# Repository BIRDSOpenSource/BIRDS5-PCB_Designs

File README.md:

<div align="center">
  
</div>

# BIRDS5-PCB_Designs
 Documentation for the PCB design files used in the boards in the BIRDS5 satellite

## About the BIRDS5 Program:

The Mission Statement of the Project is:

> Build Uganda and Zimbabwe’s first satellite while improving the standardized bus system for future missions, giving continuity to the satellite development of Japan and previous missions from BIRDS-1,2,3 and 4.

The project is led by Kyushu Institute of Technology in Japan and involves students from Uganda, Zimbabwe, Trinidad and Tobago, and Japan.

Satellite Names: Taka (Japan), ZIMSAT-1 (Zimbabwe) and PearlAfricaSat-1 (Uganda)

Stakeholders: Uganda Science, Technology and Innovation Office of the President, Zimbabwe National Geospatial And Space Agency (ZINGSA), and Kyushu Institute of Technology (Kyutech) for Japan.

Project duration: 2018-2022

CubeSat: 1U (10x10x10) cm3, 2U (10x10x20) cm3

Weight: 1.13kg

Launch Date: 21st November 2022

BIRDS-5 has 5 main missions in total; attitude visualisation, Imaging classification Mission (IMG-CLS) and Store & Forward (SF- WARD), Particle Instrument for Nano-satellite(PINO), APRS-Digipeater mission (APRS-DP) 

## Organisation structure
In this repository you will find four main folders
```bash
├── .gitattributes
├── Antenna Panel
│   ├── BIRDS-5_1U_+X-panel_EM_PUPV_v3.2.brd
│   ├── BIRDS-5_1U_+X-panel_EM_PUPV_v3.2.sch
│   ├── BIRDS-5_2U_+X-panel_EM_PUPV_v3.2.brd
│   └── BIRDS-5_2U_+X-panel_EM_PUPV_v3.2.sch
├── Back Plane Board
│   ├── BPB_FM1.brd
│   └── BPB_FM1.sch
├── LICENSE
├── README.md
├── Rear Access Board
│   ├── 1U_Rear_Access_Board
│   └── 2U_Rear_Access_Board
└── Solar Panel
    ├── EM Solar Panels
    │   ├── 1U PCB Designs
    │   ├── 2U PCB Designs
    │   └── Solar Attachment Training
    │       └── From Victor
    └── FM Solar Panels
        ├── 1U Solar Panels Data-2022_05_19
        │   ├── 1U Solar Panel PCBs
        │   ├── BOM
        │   ├── Drill Data
        │   │   ├── +Y
        │   │   │   └── CAMOutputs
        │   │   │       └── GerberFiles
        │   │   ├── +Z
        │   │   │   └── CAMOutputs
        │   │   │       └── GerberFiles
        │   │   ├── -X
        │   │   │   └── CAMOutputs
        │   │   │       └── GerberFiles
        │   │   └── -Y
        │   │       └── CAMOutputs
        │   │           └── GerberFiles
        │   ├── Gerber Data
        │   │   ├── +Y
        │   │   │   └── CAMOutputs
        │   │   │       └── GerberFiles
        │   │   ├── +Z
        │   │   │   └── CAMOutputs
        │   │   │       └── GerberFiles
        │   │   ├── -X
        │   │   │   └── CAMOutputs
        │   │   │       └── GerberFiles
        │   │   ├── -Y
        │   │   │   └── CAMOutputs
        │   │   │       └── GerberFiles
        │   │   ├── -Z
        │   │   │   └── CAMOutputs
        │   │   │       └── GerberFiles
        │   │   └── READ ME.txt
        │   ├── Mounting Drawing
        │   │   ├── +Y
        │   │   ├── +Z
        │   │   ├── -X
        │   │   ├── -Y
        │   │   └── -Z
        │   └── PBan_Parts_List
        └── 2U Solar Panels Data-2022_05_19
            ├── 2U Solar Panels PCBs
            ├── BOM
            ├── Drill Data
            │   ├── +Y
            │   │   └── CAMOutputs
            │   │       └── GerberFiles
            │   ├── -Y
            │   │   └── CAMOutputs
            │   │       └── GerberFiles
            │   └── -Z
            │       └── CAMOutputs
            │           └── GerberFiles
            ├── Gerber Data
            │   ├── +Y
            │   │   └── CAMOutputs
            │   │       └── GerberFiles
            │   ├── -Y
            │   │   └── CAMOutputs
            │   │       └── GerberFiles
            │   ├── -Z
            │   │   └── CAMOutputs
            │   │       └── GerberFiles
            ├── Mounting Drawing
            │   ├── +Y
            │   ├── -X
            │   ├── -Y
            │   └── -Z
            └── PBan Parts Lists
```
    
`/Solar Panel` folders contains PCB and schematic file for the 1U and 2U solar panel configurations. Within this folder are also pictures from the Solar Panel Attachment Training to aid in understanding how to attaach the solar cells to the panels. 

## How to use
> [!CAUTION]
> The files `.sch` and `.brd` files in this repositiry were created using Eagle software.
 
For those that want to import these files into 
KiCAD7 [here's how you do it](https://community.element14.com/technologies/open-source-hardware/b/blog/posts/working-with-kicad-7-importing-eagle-files) 
 or KiCAD5.1 [here's how you do it](https://www.youtube.com/watch?v=RBc02MwpKxk&t=1s).

> [!NOTE]
> If you are wondering "What are the .s#1 and .b#1 files?"
> They are EAGLE backup files. Each time you save your work, the previous copy becomes one of them, in case you decide you were being a muppet, or just change your mind.

## I like this project, can I help you?
You are welcome 🙂

* Give us a star ⭐
* Watch repository to be notified about updates 👀
* If you will find some errors, report them in Issues 🐞
* Try Birds designs on some real computer and let us know how it worked in Discussions. 💬
* We would greatly appreciate if you would also tell others about this ecosystem, it helps us to improve BIRDS Open Source. Thank you!

[License for this project](docs/LICENSE.md)

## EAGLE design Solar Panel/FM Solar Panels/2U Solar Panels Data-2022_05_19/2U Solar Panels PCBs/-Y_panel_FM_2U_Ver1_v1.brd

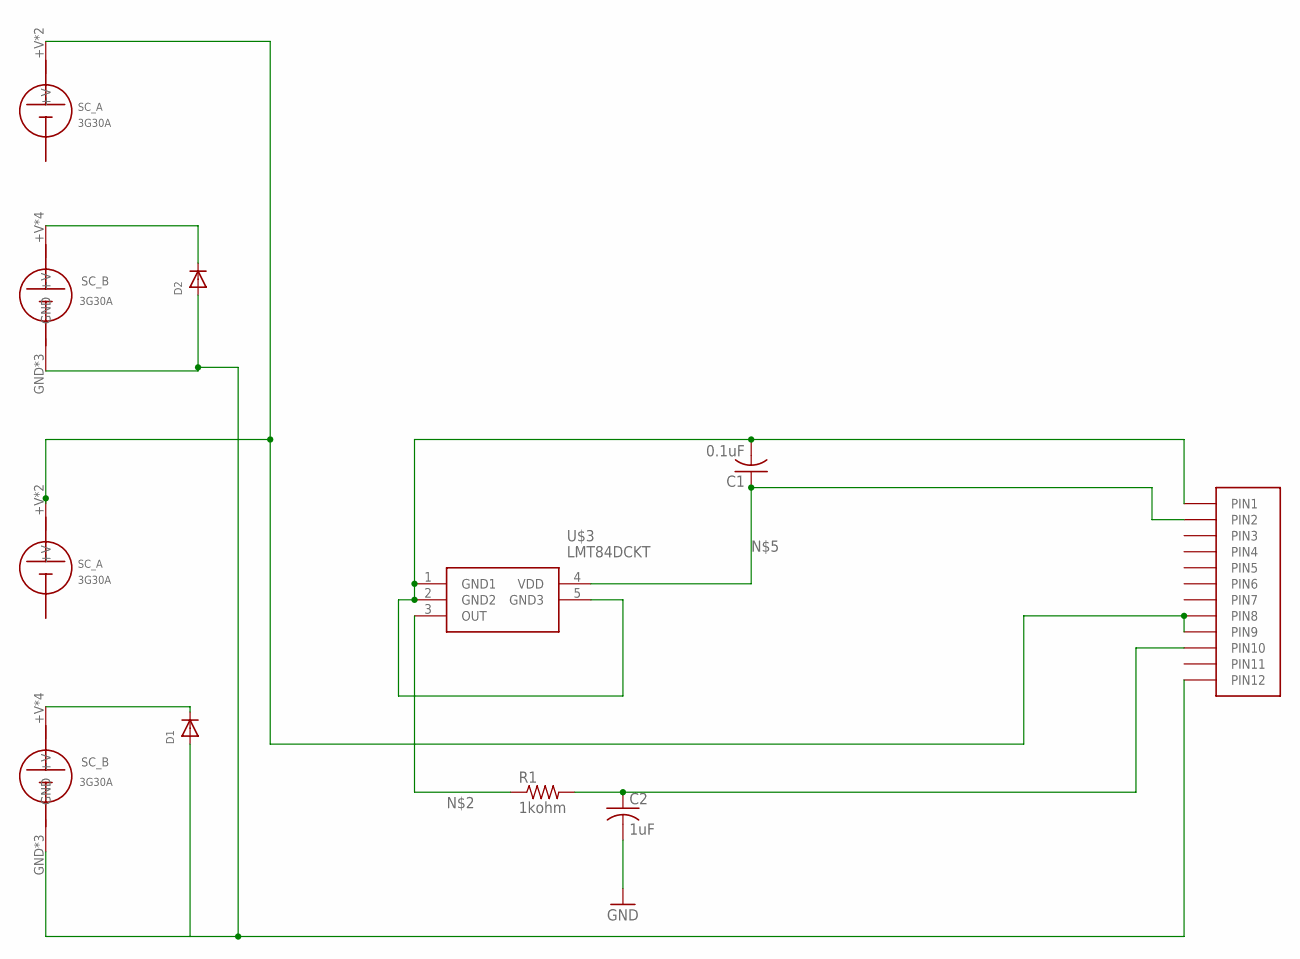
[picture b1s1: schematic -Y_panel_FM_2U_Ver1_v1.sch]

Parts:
C1: 0.1uF; C0805
C2: 1uF; C0805
D1, D2: DIODE_SOD-123FL; SOD-123FL
R1: 1kohm; R0402
SOLARCELL_A, SOLARCELL_A1: SC_A
SOLARCELL_B, SOLARCELL_B1: SC_B
U$1: HEADER12PIN
U$3: LMT84DCKT; SOT65P210X110-5N

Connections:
+V: SOLARCELL_A.+V, SOLARCELL_A.+V1, SOLARCELL_A1.+V, SOLARCELL_A1.+V1, U$1.P8 (PIN8), U$1.P9 (PIN9)
+VB: D1.C, SOLARCELL_B.+V, SOLARCELL_B.+V2 (+V), SOLARCELL_B.+V3 (+V), SOLARCELL_B.+V4 (+V)
GND: C1.2, C2.2, D1.A, D2.A, SOLARCELL_B.GND, SOLARCELL_B.GND1 (GND), SOLARCELL_B.GND2 (GND), SOLARCELL_B1.GND, SOLARCELL_B1.GND1 (GND), SOLARCELL_B1.GND2 (GND), U$1.P1 (PIN1), U$1.P12 (PIN12), U$3.1 (GND1), U$3.2 (GND2), U$3.5 (GND3)
unnamed: D2.C, SOLARCELL_B1.+V, SOLARCELL_B1.+V2 (+V), SOLARCELL_B1.+V3 (+V), SOLARCELL_B1.+V4 (+V)
unnamed: R1.1, U$3.3 (OUT)
unnamed: C1.1, U$1.P2 (PIN2), U$3.4 (VDD)
unnamed: C2.1, R1.2, U$1.P10 (PIN10)

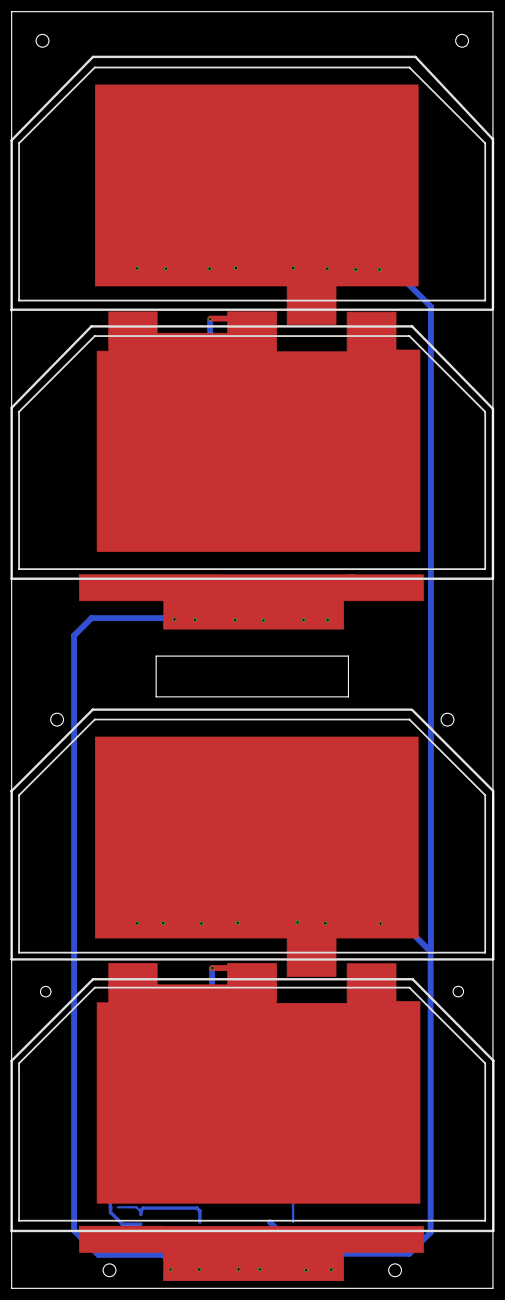
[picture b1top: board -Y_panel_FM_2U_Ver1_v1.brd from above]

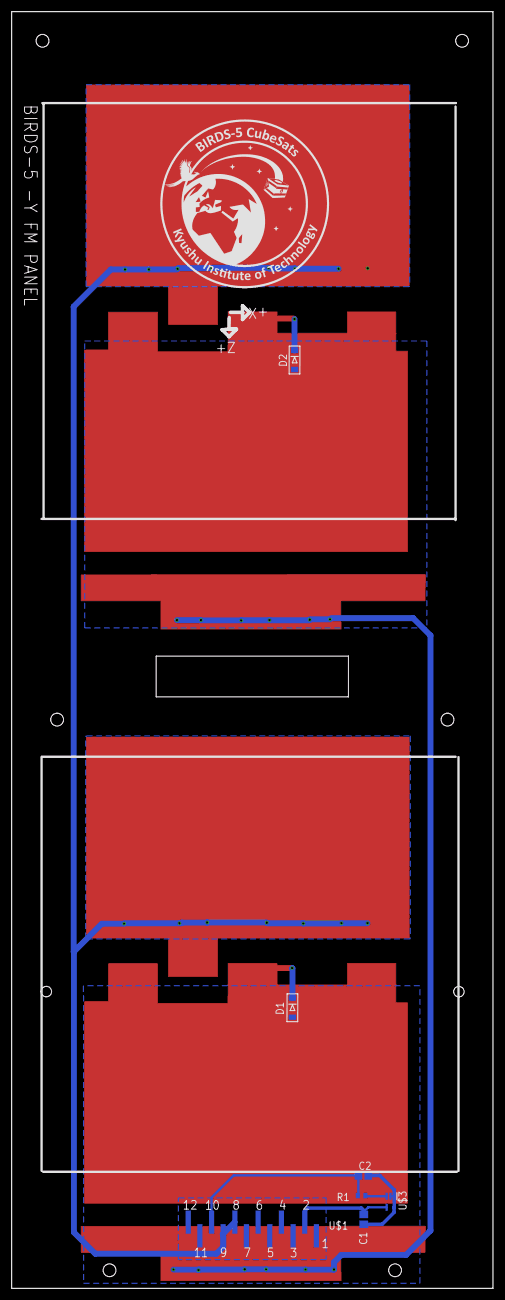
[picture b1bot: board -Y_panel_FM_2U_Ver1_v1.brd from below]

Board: 2 copper layers, 82.6 x 219.1 mm, 11 parts (5 on the bottom side), 7 nets.

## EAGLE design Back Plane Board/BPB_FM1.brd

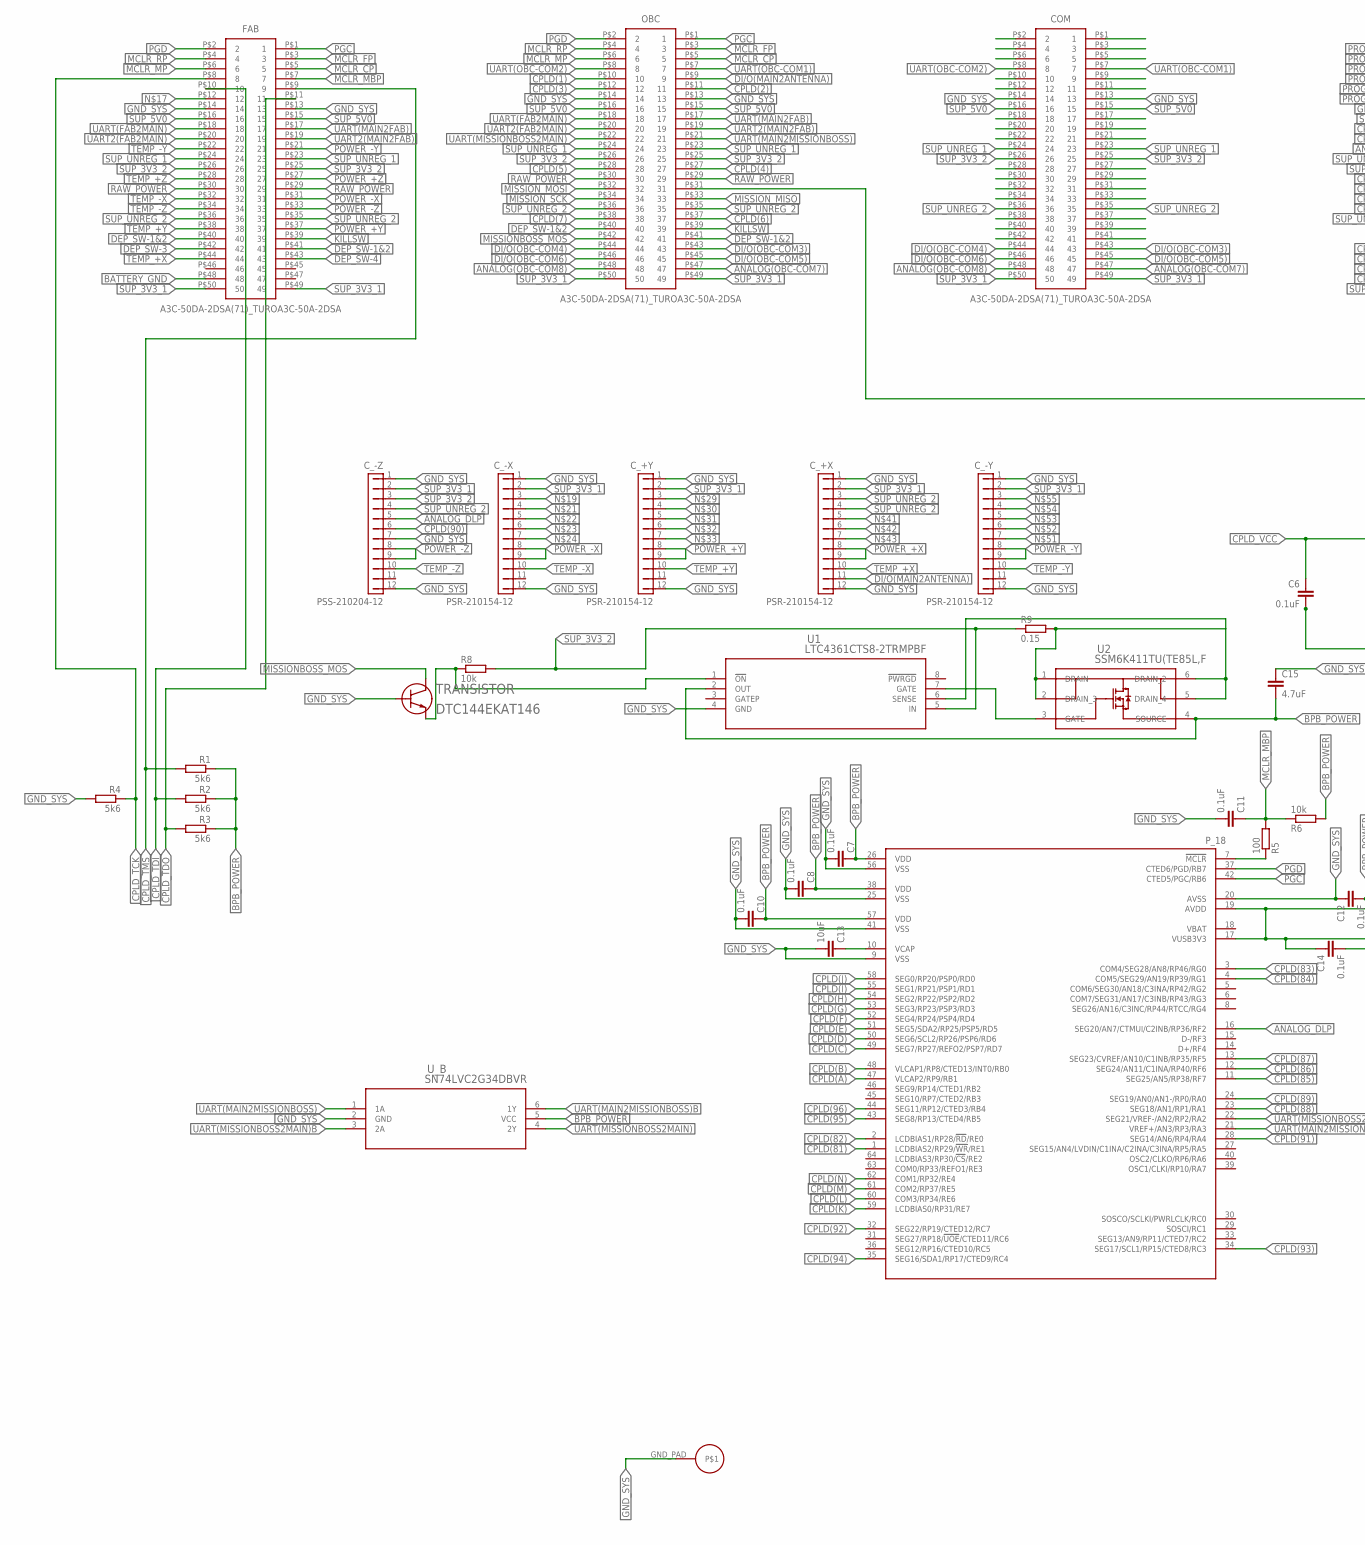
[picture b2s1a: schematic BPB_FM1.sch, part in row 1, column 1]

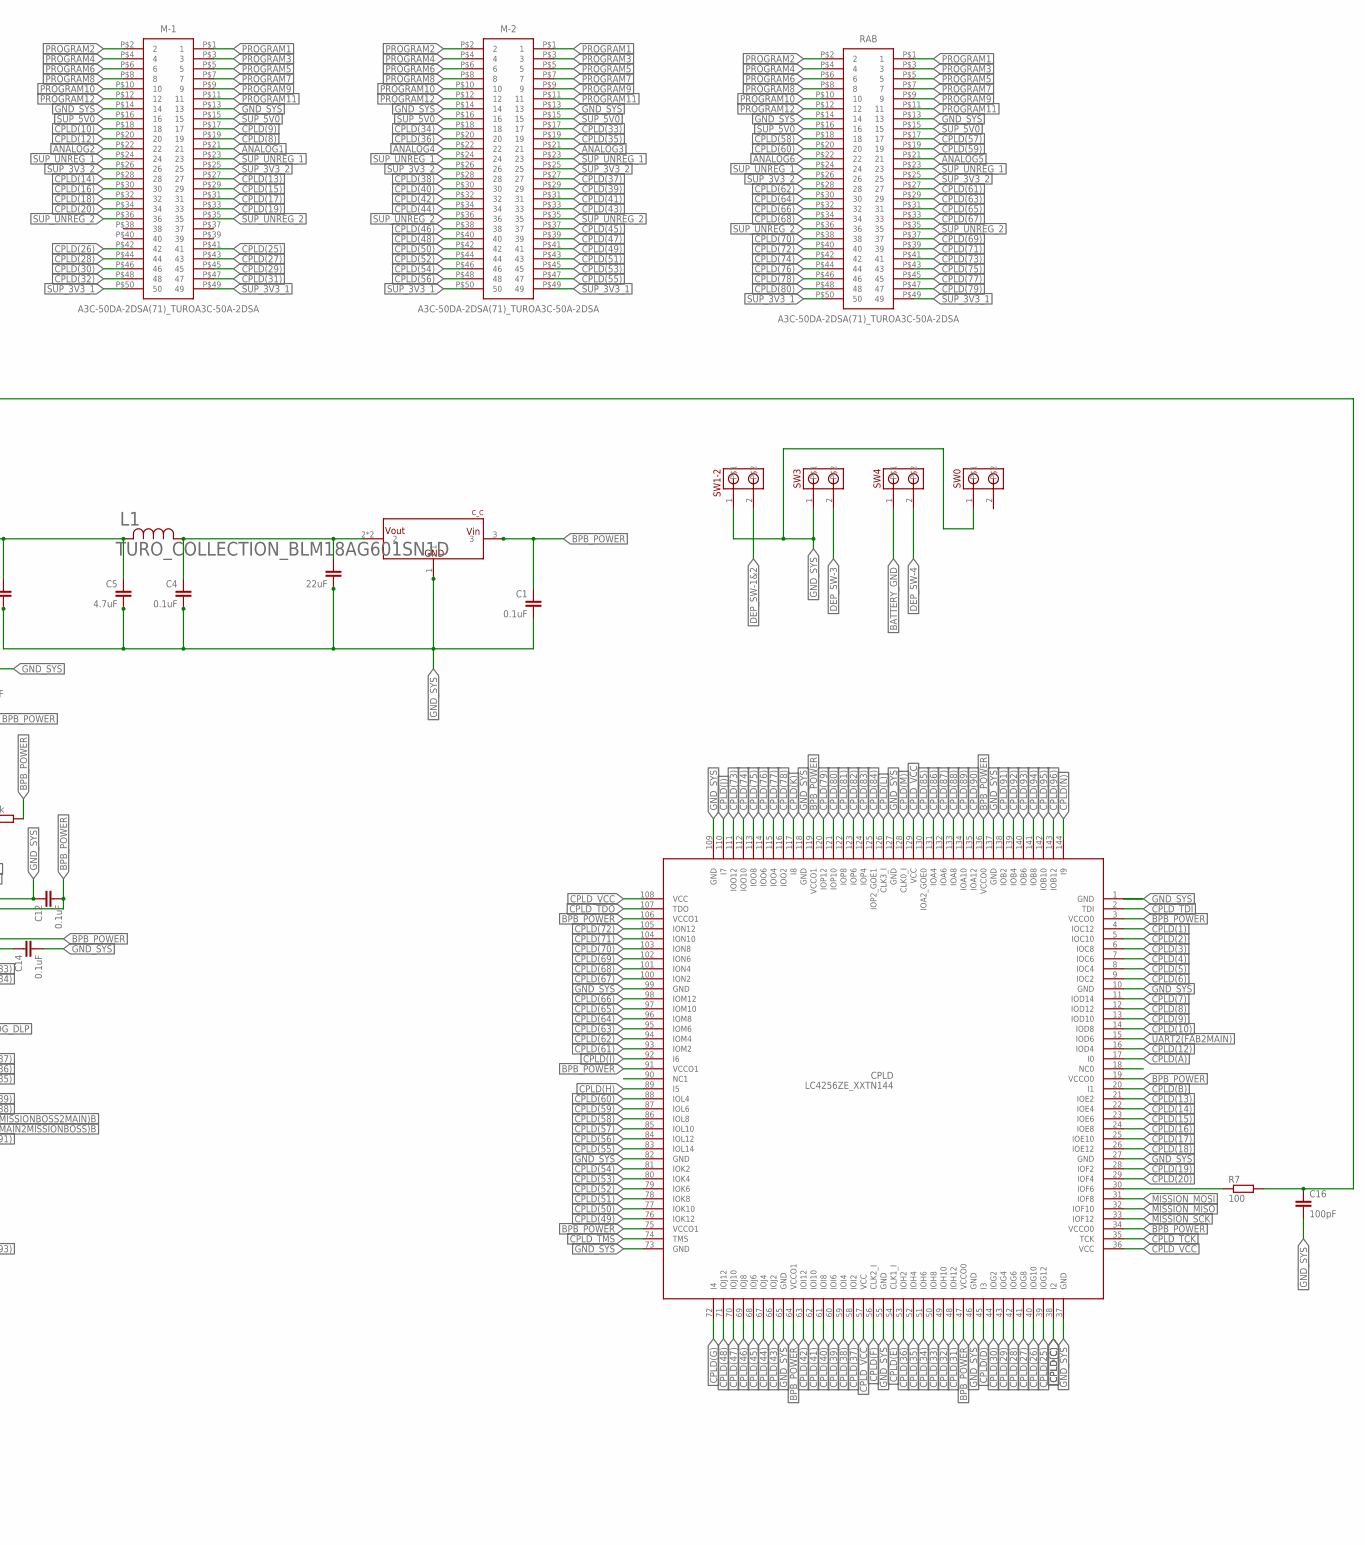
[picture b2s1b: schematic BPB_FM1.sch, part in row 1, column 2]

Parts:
C1, C4, C6, C7, C8, C10, C11, C12, C14: 0.1uF; C0402
C3: 22uF; C2012
C5: 4.7uF; C2012
C13: 10uF; C0402
C15: 4.7uF; C0402
C16: 100pF; C0402
COM: A3C-50DA-2DSA(71)_TUROA3C-50A-2DSA; SHDR50W60P200_2X25_5000X400X44_TR
CPLD: LC4256ZE_XXTN144; TQFP144
C_+X: PSR-210154-12; PIN1X12/90
C_+Y: PSR-210154-12; PIN1X12/90
C_-X: PSR-210154-12; PIN1X12/90
C_-Y: PSR-210154-12; PIN1X12/90
C_-Z: PSS-210204-12; PIN1X12
C_C: NCV1117ST18T3G; SOT223
FAB: A3C-50DA-2DSA(71)_TUROA3C-50A-2DSA; SHDR50W60P200_2X25_5000X400X44_TR
L1: TURO_COLLECTION_BLM18AG601SN1D; TURO_COLLECTION_IND_BLM18_0603
M-1, M-2: A3C-50DA-2DSA(71)_TUROA3C-50A-2DSA; SHDR50W60P200_2X25_5000X400X44_TR
OBC: A3C-50DA-2DSA(71)_TUROA3C-50A-2DSA; SHDR50W60P200_2X25_5000X400X44_TR
P_18: PIC18F67J94; PIC18F67J9_SMA_LEAD
R1, R2, R3, R4: 5k6; R0402
R5, R7: 100; R0402
R6, R8: 10k; R0402
R9: 0.15; R0402
RAB: A3C-50DA-2DSA(71)_TUROA3C-50A-2DSA; SHDR50W60P200_2X25_5000X400X44_TR
SW0, SW1-2, SW3, SW4: MOLEX-CONN-2-0554600272; MOLEX-CONN-2-BIRDS
TRANSISTOR: DTC144EKAT146; TRANS_DTA113TKAT_ROM
U1: LTC4361CTS8-2TRMPBF; TSOT-23_TS8_LIT
U2: SSM6K411TU(TE85L,F; SON_E85L,F_TOS
U$1: GND_PAD
U_B: SN74LVC2G34DBVR; DBV6

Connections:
ANALOG1: M-1.P$21 (21)
ANALOG2: M-1.P$22 (22)
ANALOG3: M-2.P$21 (21)
ANALOG4: M-2.P$22 (22)
ANALOG5: RAB.P$21 (21)
ANALOG6: RAB.P$22 (22)
ANALOG(OBC-COM7): COM.P$47 (47), OBC.P$47 (47)
ANALOG(OBC-COM8): COM.P$48 (48), OBC.P$48 (48)
ANALOG_DLP: C_-Z.5, P_18.16 (SEG20/AN7/CTMUI/C2INB/RP36/RF2)
BATTERY_GND: FAB.P$48 (48), SW4.1
BPB_POWER: C1.1, C7.1, C8.1, C10.1, C12.2, C14.1, C15.2, CPLD.3 (VCCO0), CPLD.19 (VCCO0), CPLD.34 (VCCO0), CPLD.47 (VCCO0), CPLD.64 (VCCO1), CPLD.75 (VCCO1), CPLD.91 (VCCO1), CPLD.106 (VCCO1), CPLD.119 (VCCO1), CPLD.136 (VCCO0), C_C.3, P_18.17 (VUSB3V3), P_18.19 (AVDD), P_18.26 (VDD), P_18.38 (VDD), P_18.57 (VDD), R1.1, R2.1, R3.1, R6.2, U1.2 (OUT), U2.4 (SOURCE), U_B.5 (VCC)
CPLD(1): CPLD.4 (IOC12), OBC.P$10 (10)
CPLD(2): CPLD.5 (IOC10), OBC.P$11 (11)
CPLD(3): CPLD.6 (IOC8), OBC.P$12 (12)
CPLD(4): CPLD.7 (IOC6), OBC.P$27 (27)
CPLD(5): CPLD.8 (IOC4), OBC.P$28 (28)
CPLD(6): CPLD.9 (IOC2), OBC.P$37 (37)
CPLD(7): CPLD.11 (IOD14), OBC.P$38 (38)
CPLD(8): CPLD.12 (IOD12), M-1.P$19 (19)
CPLD(9): CPLD.13 (IOD10), M-1.P$17 (17)
CPLD(10): CPLD.14 (IOD8), M-1.P$18 (18)
CPLD(12): CPLD.16 (IOD4), M-1.P$20 (20)
CPLD(13): CPLD.21 (IOE2), M-1.P$27 (27)
CPLD(14): CPLD.22 (IOE4), M-1.P$28 (28)
CPLD(15): CPLD.23 (IOE6), M-1.P$29 (29)
CPLD(16): CPLD.24 (IOE8), M-1.P$30 (30)
CPLD(17): CPLD.25 (IOE10), M-1.P$31 (31)
CPLD(18): CPLD.26 (IOE12), M-1.P$32 (32)
CPLD(19): CPLD.28 (IOF2), M-1.P$33 (33)
CPLD(20): CPLD.29 (IOF4), M-1.P$34 (34)
CPLD(25): CPLD.39 (IOG12), M-1.P$41 (41)
CPLD(26): CPLD.40 (IOG10), M-1.P$42 (42)
CPLD(27): CPLD.41 (IOG8), M-1.P$43 (43)
CPLD(28): CPLD.42 (IOG6), M-1.P$44 (44)
CPLD(29): CPLD.43 (IOG4), M-1.P$45 (45)
CPLD(30): CPLD.44 (IOG2), M-1.P$46 (46)
CPLD(31): CPLD.48 (IOH12), M-1.P$47 (47)
CPLD(32): CPLD.49 (IOH10), M-1.P$48 (48)
CPLD(33): CPLD.50 (IOH8), M-2.P$17 (17)
CPLD(34): CPLD.51 (IOH6), M-2.P$18 (18)
CPLD(35): CPLD.52 (IOH4), M-2.P$19 (19)
CPLD(36): CPLD.53 (IOH2), M-2.P$20 (20)
CPLD(37): CPLD.58 (IOI2), M-2.P$27 (27)
CPLD(38): CPLD.59 (IOI4), M-2.P$28 (28)
CPLD(39): CPLD.60 (IOI6), M-2.P$29 (29)
CPLD(40): CPLD.61 (IOI8), M-2.P$30 (30)
CPLD(41): CPLD.62 (IOI10), M-2.P$31 (31)
CPLD(42): CPLD.63 (IOI12), M-2.P$32 (32)
CPLD(43): CPLD.66 (IOJ2), M-2.P$33 (33)
CPLD(44): CPLD.67 (IOJ4), M-2.P$34 (34)
CPLD(45): CPLD.68 (IOJ6), M-2.P$37 (37)
CPLD(46): CPLD.69 (IOJ8), M-2.P$38 (38)
CPLD(47): CPLD.70 (IOJ10), M-2.P$39 (39)
CPLD(48): CPLD.71 (IOJ12), M-2.P$40 (40)
CPLD(49): CPLD.76 (IOK12), M-2.P$41 (41)
CPLD(50): CPLD.77 (IOK10), M-2.P$42 (42)
CPLD(51): CPLD.78 (IOK8), M-2.P$43 (43)
CPLD(52): CPLD.79 (IOK6), M-2.P$44 (44)
CPLD(53): CPLD.80 (IOK4), M-2.P$45 (45)
CPLD(54): CPLD.81 (IOK2), M-2.P$46 (46)
CPLD(55): CPLD.83 (IOL14), M-2.P$47 (47)
CPLD(56): CPLD.84 (IOL12), M-2.P$48 (48)
CPLD(57): CPLD.85 (IOL10), RAB.P$17 (17)
CPLD(58): CPLD.86 (IOL8), RAB.P$18 (18)
CPLD(59): CPLD.87 (IOL6), RAB.P$19 (19)
CPLD(60): CPLD.88 (IOL4), RAB.P$20 (20)
CPLD(61): CPLD.93 (IOM2), RAB.P$27 (27)
CPLD(62): CPLD.94 (IOM4), RAB.P$28 (28)
CPLD(63): CPLD.95 (IOM6), RAB.P$29 (29)
CPLD(64): CPLD.96 (IOM8), RAB.P$30 (30)
CPLD(65): CPLD.97 (IOM10), RAB.P$31 (31)
CPLD(66): CPLD.98 (IOM12), RAB.P$32 (32)
CPLD(67): CPLD.100 (ION2), RAB.P$33 (33)
CPLD(68): CPLD.101 (ION4), RAB.P$34 (34)
CPLD(69): CPLD.102 (ION6), RAB.P$37 (37)
CPLD(70): CPLD.103 (ION8), RAB.P$38 (38)
CPLD(71): CPLD.104 (ION10), RAB.P$39 (39)
CPLD(72): CPLD.105 (ION12), RAB.P$40 (40)
CPLD(73): CPLD.111 (IOO12), RAB.P$41 (41)
CPLD(74): CPLD.112 (IOO10), RAB.P$42 (42)
CPLD(75): CPLD.113 (IOO8), RAB.P$43 (43)
CPLD(76): CPLD.114 (IOO6), RAB.P$44 (44)
CPLD(77): CPLD.115 (IOO4), RAB.P$45 (45)
CPLD(78): CPLD.116 (IOO2), RAB.P$46 (46)
CPLD(79): CPLD.120 (IOP12), RAB.P$47 (47)
CPLD(80): CPLD.121 (IOP10), RAB.P$48 (48)
CPLD(81): CPLD.122 (IOP8), P_18.1 (LCDBIAS2/RP29/!WR!/RE1)
CPLD(82): CPLD.123 (IOP6), P_18.2 (LCDBIAS1/RP28/!RD!/RE0)
CPLD(83): CPLD.124 (IOP4), P_18.3 (COM4/SEG28/AN8/RP46/RG0)
CPLD(84): CPLD.125 (IOP2_GOE1), P_18.4 (COM5/SEG29/AN19/RP39/RG1)
CPLD(85): CPLD.130 (IOA2_GOE0), P_18.11 (SEG25/AN5/RP38/RF7)
CPLD(86): CPLD.131 (IOA4), P_18.12 (SEG24/AN11/C1INA/RP40/RF6)
CPLD(87): CPLD.132 (IOA6), P_18.13 (SEG23/CVREF/AN10/C1INB/RP35/RF5)
CPLD(88): CPLD.133 (IOA8), P_18.23 (SEG18/AN1/RP1/RA1)
CPLD(89): CPLD.134 (IOA10), P_18.24 (SEG19/AN0/AN1-/RP0/RA0)
CPLD(90): CPLD.135 (IOA12), C_-Z.6
CPLD(91): CPLD.138 (IOB2), P_18.28 (SEG14/AN6/RP4/RA4)
CPLD(92): CPLD.139 (IOB4), P_18.32 (SEG22/RP19/CTED12/RC7)
CPLD(93): CPLD.140 (IOB6), P_18.34 (SEG17/SCL1/RP15/CTED8/RC3)
CPLD(94): CPLD.141 (IOB8), P_18.35 (SEG16/SDA1/RP17/CTED9/RC4)
CPLD(95): CPLD.142 (IOB10), P_18.43 (SEG8/RP13/CTED4/RB5)
CPLD(96): CPLD.143 (IOB12), P_18.44 (SEG11/RP12/CTED3/RB4)
CPLD(A): CPLD.17 (I0), P_18.47 (VLCAP2/RP9/RB1)
CPLD(B): CPLD.20 (I1), P_18.48 (VLCAP1/RP8/CTED13/INT0/RB0)
CPLD(C): CPLD.38 (I2), P_18.49 (SEG7/RP27/REFO2/PSP7/RD7)
CPLD(D): CPLD.45 (I3), P_18.50 (SEG6/SCL2/RP26/PSP6/RD6)
CPLD(E): CPLD.54 (CLK1_I), P_18.51 (SEG5/SDA2/RP25/PSP5/RD5)
CPLD(F): CPLD.56 (CLK2_I), P_18.52 (SEG4/RP24/PSP4/RD4)
CPLD(G): CPLD.72 (I4), P_18.53 (SEG3/RP23/PSP3/RD3)
CPLD(H): CPLD.89 (I5), P_18.54 (SEG2/RP22/PSP2/RD2)
CPLD(I): CPLD.92 (I6), P_18.55 (SEG1/RP21/PSP1/RD1)
CPLD(J): CPLD.110 (I7), P_18.58 (SEG0/RP20/PSP0/RD0)
CPLD(K): CPLD.117 (I8), P_18.59 (LCDBIAS0/RP31/RE7)
CPLD(L): CPLD.126 (CLK3_I), P_18.60 (COM3/RP34/RE6)
CPLD(M): CPLD.128 (CLK0_I), P_18.61 (COM2/RP37/RE5)
CPLD(N): CPLD.144 (I9), P_18.62 (COM1/RP32/RE4)
CPLD_TCK: CPLD.35 (TCK), FAB.P$8 (8), R4.1
CPLD_TDI: CPLD.2 (TDI), FAB.P$10 (10), R2.2
CPLD_TDO: CPLD.107 (TDO), FAB.P$11 (11), R3.2
CPLD_TMS: CPLD.74 (TMS), FAB.P$9 (9), R1.2
CPLD_VCC: C5.1, C6.1, CPLD.36 (VCC), CPLD.57 (VCC), CPLD.108 (VCC), CPLD.129 (VCC), L1.2
DEP_SW-1&2: FAB.P$40 (40), FAB.P$41 (41), OBC.P$40 (40), OBC.P$41 (41), SW1-2.2
DEP_SW-3: FAB.P$42 (42), SW3.2
DEP_SW-4: FAB.P$43 (43), SW4.2
DI/O(MAIN2ANTENNA): C_+X.11, OBC.P$9 (9)
DI/O(OBC-COM3): COM.P$43 (43), OBC.P$43 (43)
DI/O(OBC-COM4): COM.P$44 (44), OBC.P$44 (44)
DI/O(OBC-COM5): COM.P$45 (45), OBC.P$45 (45)
DI/O(OBC-COM6): COM.P$46 (46), OBC.P$46 (46)
GND_SYS: C1.2, C3.2, C4.2, C5.2, C6.2, C7.2, C8.2, C10.2, C11.2, C12.1, C13.2, C14.2, C15.1, C16.2, COM.P$13 (13), COM.P$14 (14), CPLD.1 (GND), CPLD.10 (GND), CPLD.27 (GND), CPLD.37 (GND), CPLD.46 (GND), CPLD.55 (GND), CPLD.65 (GND), CPLD.73 (GND), CPLD.82 (GND), CPLD.99 (GND), CPLD.109 (GND), CPLD.118 (GND), CPLD.127 (GND), CPLD.137 (GND), C_+X.1, C_+X.12, C_+Y.1, C_+Y.12, C_-X.1, C_-X.12, C_-Y.1, C_-Y.12, C_-Z.1, C_-Z.7, C_-Z.12, C_C.1, FAB.P$13 (13), FAB.P$14 (14), M-1.P$13 (13), M-1.P$14 (14), M-2.P$13 (13), M-2.P$14 (14), OBC.P$13 (13), OBC.P$14 (14), P_18.9 (VSS), P_18.20 (AVSS), P_18.25 (VSS), P_18.41 (VSS), P_18.56 (VSS), R4.2, RAB.P$13 (13), RAB.P$14 (14), SW0.1, SW1-2.1, SW3.1, TRANSISTOR.2 (11), U1.4 (GND), U$1.GND_PAD, U_B.2 (GND)
KILLSW: FAB.P$39 (39), OBC.P$39 (39)
MCLR_CP: FAB.P$5 (5), OBC.P$5 (5)
MCLR_FP: FAB.P$3 (3), OBC.P$3 (3)
MCLR_MBP: C11.1, FAB.P$7 (7), R5.2, R6.1
MCLR_MP: FAB.P$6 (6), OBC.P$6 (6)
MCLR_RP: FAB.P$4 (4), OBC.P$4 (4)
MISSIONBOSS_MOS: OBC.P$42 (42), TRANSISTOR.1 (12)
MISSION_CS: C16.1, OBC.P$31 (31), R7.2
MISSION_MISO: CPLD.32 (IOF10), OBC.P$33 (33)
MISSION_MOSI: CPLD.31 (IOF8), OBC.P$32 (32)
MISSION_SCK: CPLD.33 (IOF12), OBC.P$34 (34)
unnamed: P_18.7 (!MCLR!), R5.1
unnamed: CPLD.30 (IOF6), R7.1
unnamed: R8.1, TRANSISTOR.3 (13), U1.1 (!ON)
unnamed: R9.2, U1.6 (SENSE), U2.1 (DRAIN), U2.2 (DRAIN_3), U2.5 (DRAIN_4), U2.6 (DRAIN_2)
unnamed: C13.1, P_18.10 (VCAP)
unnamed: U1.7 (GATE), U2.3 (GATE)
unnamed: C3.1, C4.1, C_C.2, C_C.4 (2), L1.1
PGC: FAB.P$1 (1), OBC.P$1 (1), P_18.42 (CTED5/PGC/RB6)
PGD: FAB.P$2 (2), OBC.P$2 (2), P_18.37 (CTED6/PGD/RB7)
POWER_+X: C_+X.8, C_+X.9
POWER_+Y: C_+Y.8, C_+Y.9, FAB.P$37 (37)
POWER_+Z: FAB.P$27 (27)
POWER_-X: C_-X.8, C_-X.9, FAB.P$31 (31)
POWER_-Y: C_-Y.8, C_-Y.9, FAB.P$21 (21)
POWER_-Z: C_-Z.8, C_-Z.9, FAB.P$33 (33)
PROGRAM1: M-1.P$1 (1), M-2.P$1 (1), RAB.P$1 (1)
PROGRAM2: M-1.P$2 (2), M-2.P$2 (2), RAB.P$2 (2)
PROGRAM3: M-1.P$3 (3), M-2.P$3 (3), RAB.P$3 (3)
PROGRAM4: M-1.P$4 (4), M-2.P$4 (4), RAB.P$4 (4)
PROGRAM5: M-1.P$5 (5), M-2.P$5 (5), RAB.P$5 (5)
PROGRAM6: M-1.P$6 (6), M-2.P$6 (6), RAB.P$6 (6)
PROGRAM7: M-1.P$7 (7), M-2.P$7 (7), RAB.P$7 (7)
PROGRAM8: M-1.P$8 (8), M-2.P$8 (8), RAB.P$8 (8)
PROGRAM9: M-1.P$9 (9), M-2.P$9 (9), RAB.P$9 (9)
PROGRAM10: M-1.P$10 (10), M-2.P$10 (10), RAB.P$10 (10)
PROGRAM11: M-1.P$11 (11), M-2.P$11 (11), RAB.P$11 (11)
PROGRAM12: M-1.P$12 (12), M-2.P$12 (12), RAB.P$12 (12)
RAW_POWER: FAB.P$29 (29), FAB.P$30 (30), OBC.P$29 (29), OBC.P$30 (30)
SUP_3V3_1: COM.P$49 (49), COM.P$50 (50), C_+X.2, C_+Y.2, C_-X.2, C_-Y.2, C_-Z.2, FAB.P$49 (49), FAB.P$50 (50), M-1.P$49 (49), M-1.P$50 (50), M-2.P$49 (49), M-2.P$50 (50), OBC.P$49 (49), OBC.P$50 (50), RAB.P$49 (49), RAB.P$50 (50)
SUP_3V3_2: COM.P$25 (25), COM.P$26 (26), C_-Z.3, FAB.P$25 (25), FAB.P$26 (26), M-1.P$25 (25), M-1.P$26 (26), M-2.P$25 (25), M-2.P$26 (26), OBC.P$25 (25), OBC.P$26 (26), R8.2, R9.1, RAB.P$25 (25), RAB.P$26 (26), U1.5 (IN)
SUP_5V0: COM.P$15 (15), COM.P$16 (16), FAB.P$15 (15), FAB.P$16 (16), M-1.P$15 (15), M-1.P$16 (16), M-2.P$15 (15), M-2.P$16 (16), OBC.P$15 (15), OBC.P$16 (16), RAB.P$15 (15), RAB.P$16 (16)
SUP_UNREG_1: COM.P$23 (23), COM.P$24 (24), FAB.P$23 (23), FAB.P$24 (24), M-1.P$23 (23), M-1.P$24 (24), M-2.P$23 (23), M-2.P$24 (24), OBC.P$23 (23), OBC.P$24 (24), RAB.P$23 (23), RAB.P$24 (24)
SUP_UNREG_2: COM.P$35 (35), COM.P$36 (36), C_+X.3, C_+X.4, C_-Z.4, FAB.P$35 (35), FAB.P$36 (36), M-1.P$35 (35), M-1.P$36 (36), M-2.P$35 (35), M-2.P$36 (36), OBC.P$35 (35), OBC.P$36 (36), RAB.P$35 (35), RAB.P$36 (36)
TEMP_+X: C_+X.10, FAB.P$44 (44)
TEMP_+Y: C_+Y.10, FAB.P$38 (38)
TEMP_+Z: FAB.P$28 (28)
TEMP_-X: C_-X.10, FAB.P$32 (32)
TEMP_-Y: C_-Y.10, FAB.P$22 (22)
TEMP_-Z: C_-Z.10, FAB.P$34 (34)
UART2(FAB2MAIN): CPLD.15 (IOD6), FAB.P$20 (20), OBC.P$20 (20)
UART2(MAIN2FAB): FAB.P$19 (19), OBC.P$19 (19)
UART(FAB2MAIN): FAB.P$18 (18), OBC.P$18 (18)
UART(MAIN2FAB): FAB.P$17 (17), OBC.P$17 (17)
UART(MAIN2MISSIONBOSS): OBC.P$21 (21), U_B.1 (1A)
UART(MAIN2MISSIONBOSS)B: P_18.21 (VREF+/AN3/RP3/RA3), U_B.6 (1Y)
UART(MISSIONBOSS2MAIN): OBC.P$22 (22), U_B.4 (2Y)
UART(MISSIONBOSS2MAIN)B: P_18.22 (SEG21/VREF-/AN2/RP2/RA2), U_B.3 (2A)
UART(OBC-COM1): COM.P$7 (7), OBC.P$7 (7)
UART(OBC-COM2): COM.P$8 (8), OBC.P$8 (8)

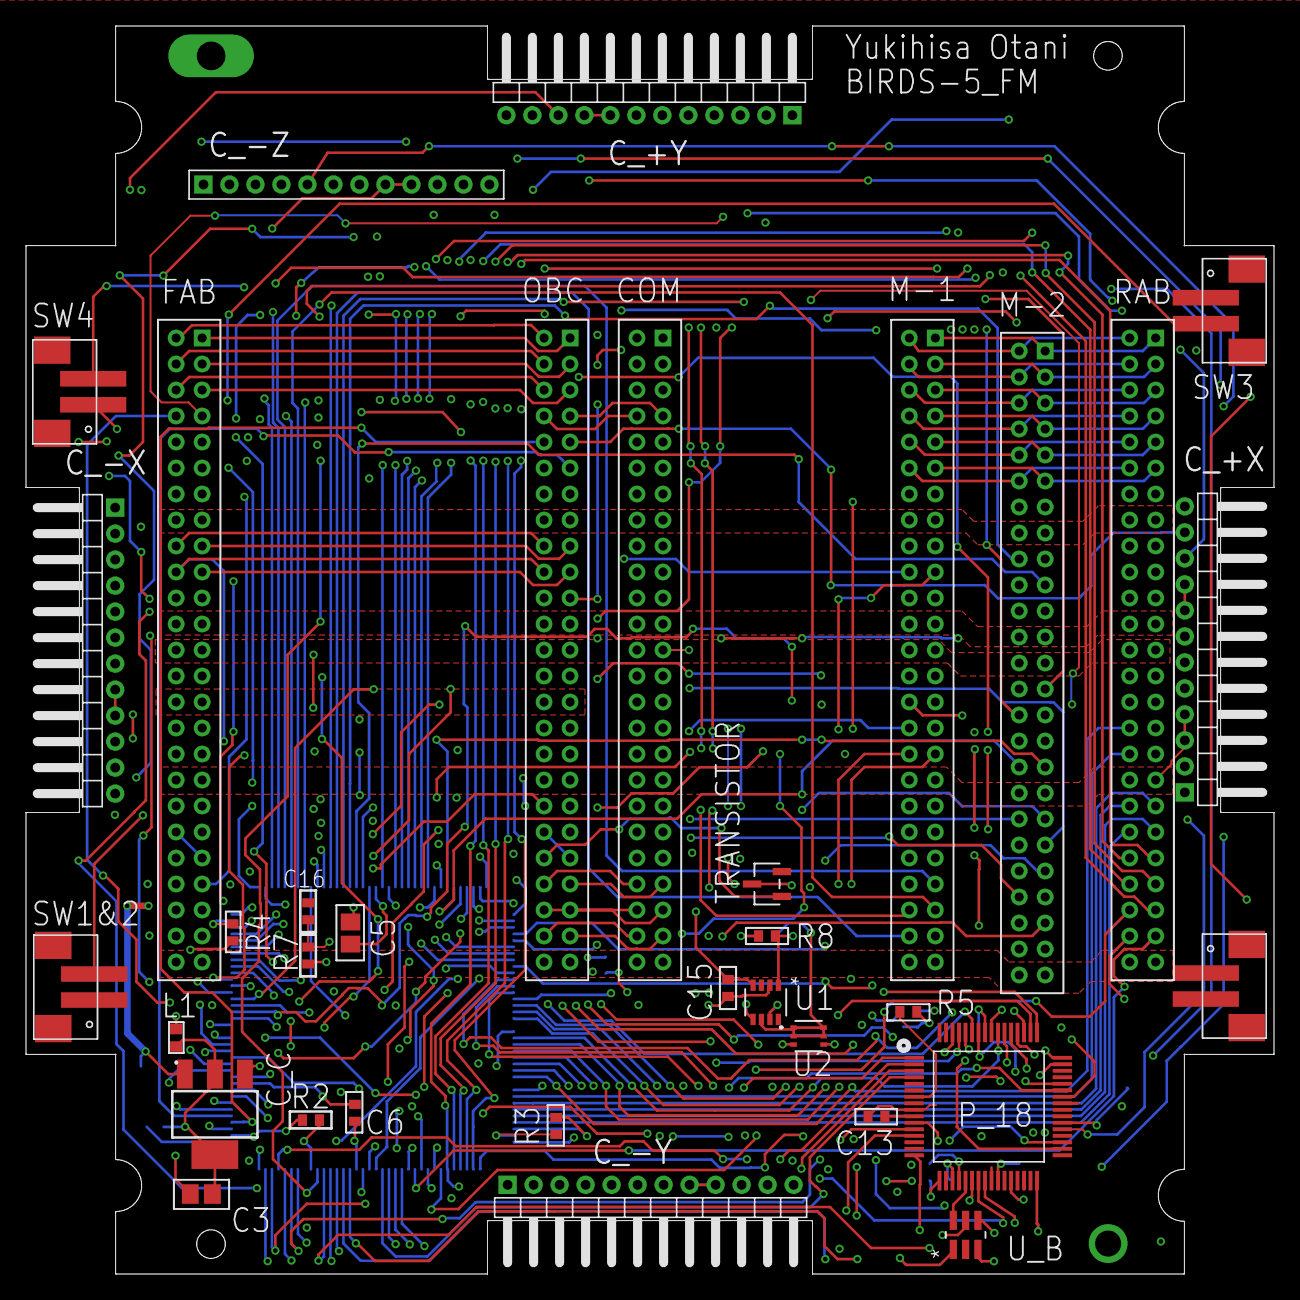
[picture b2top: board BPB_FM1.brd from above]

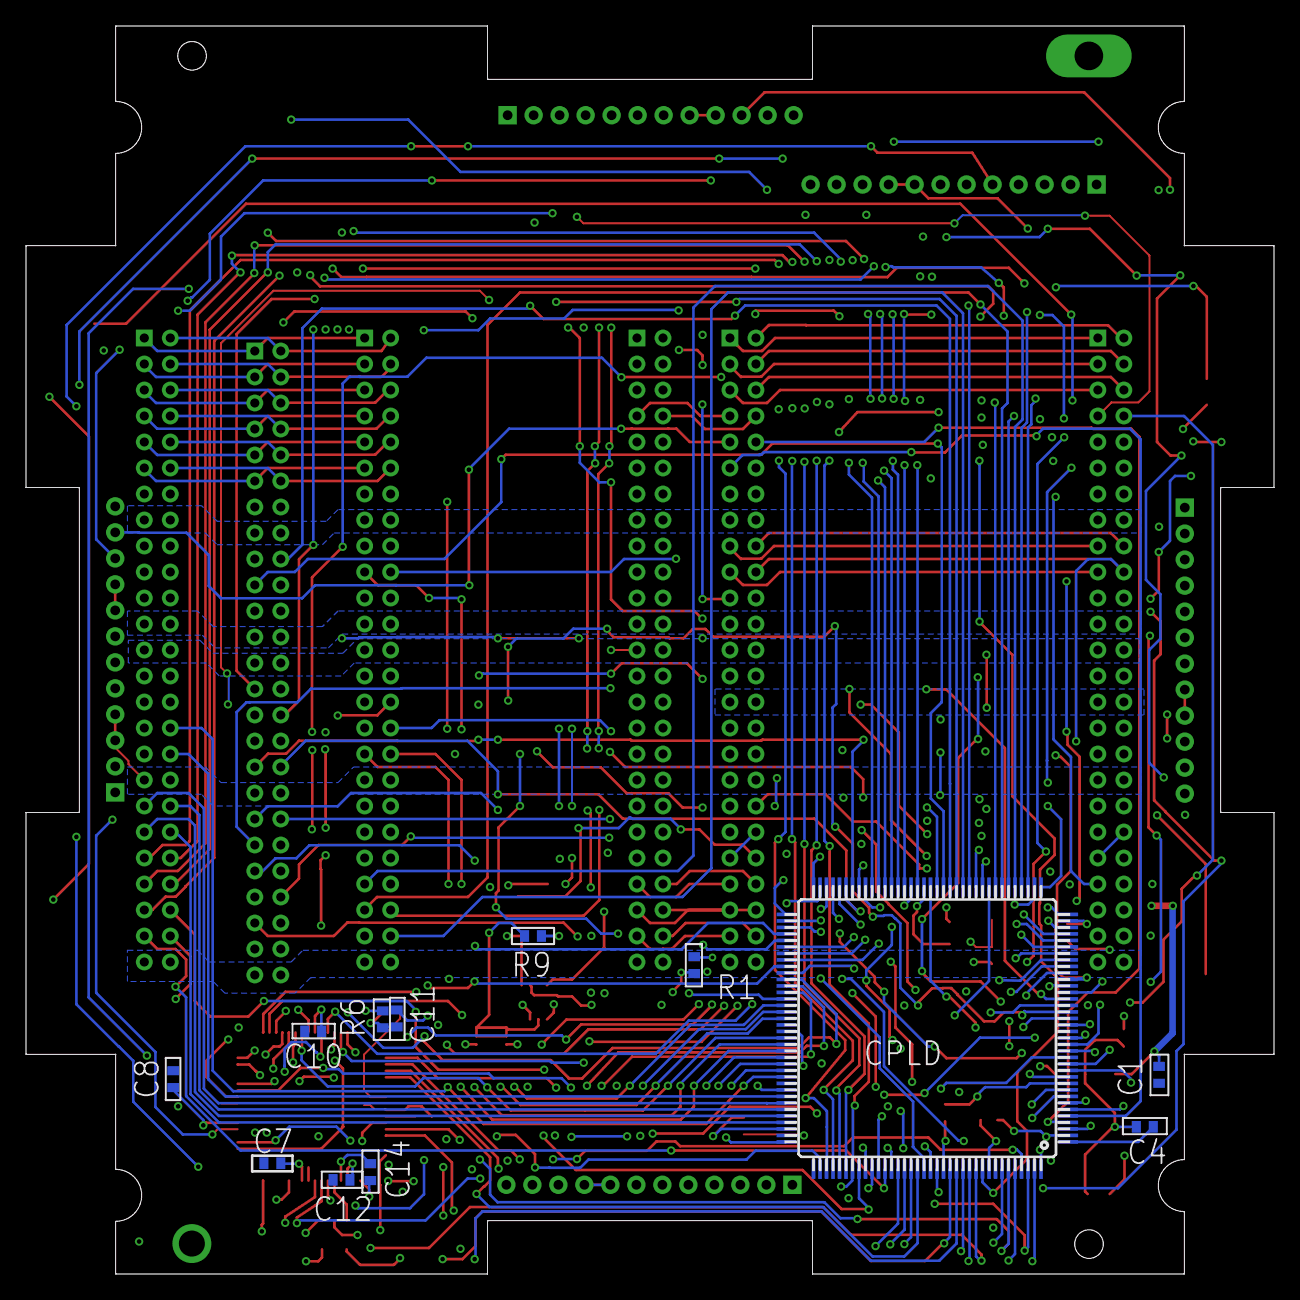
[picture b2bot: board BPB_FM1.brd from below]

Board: 6 copper layers, 96.0 x 96.0 mm, 47 parts (12 on the bottom side), 182 nets.

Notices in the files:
parts and their libraries:
COPYRIGHT: Copyright (C) 2018 Accelerated Designs. All rights reserved
